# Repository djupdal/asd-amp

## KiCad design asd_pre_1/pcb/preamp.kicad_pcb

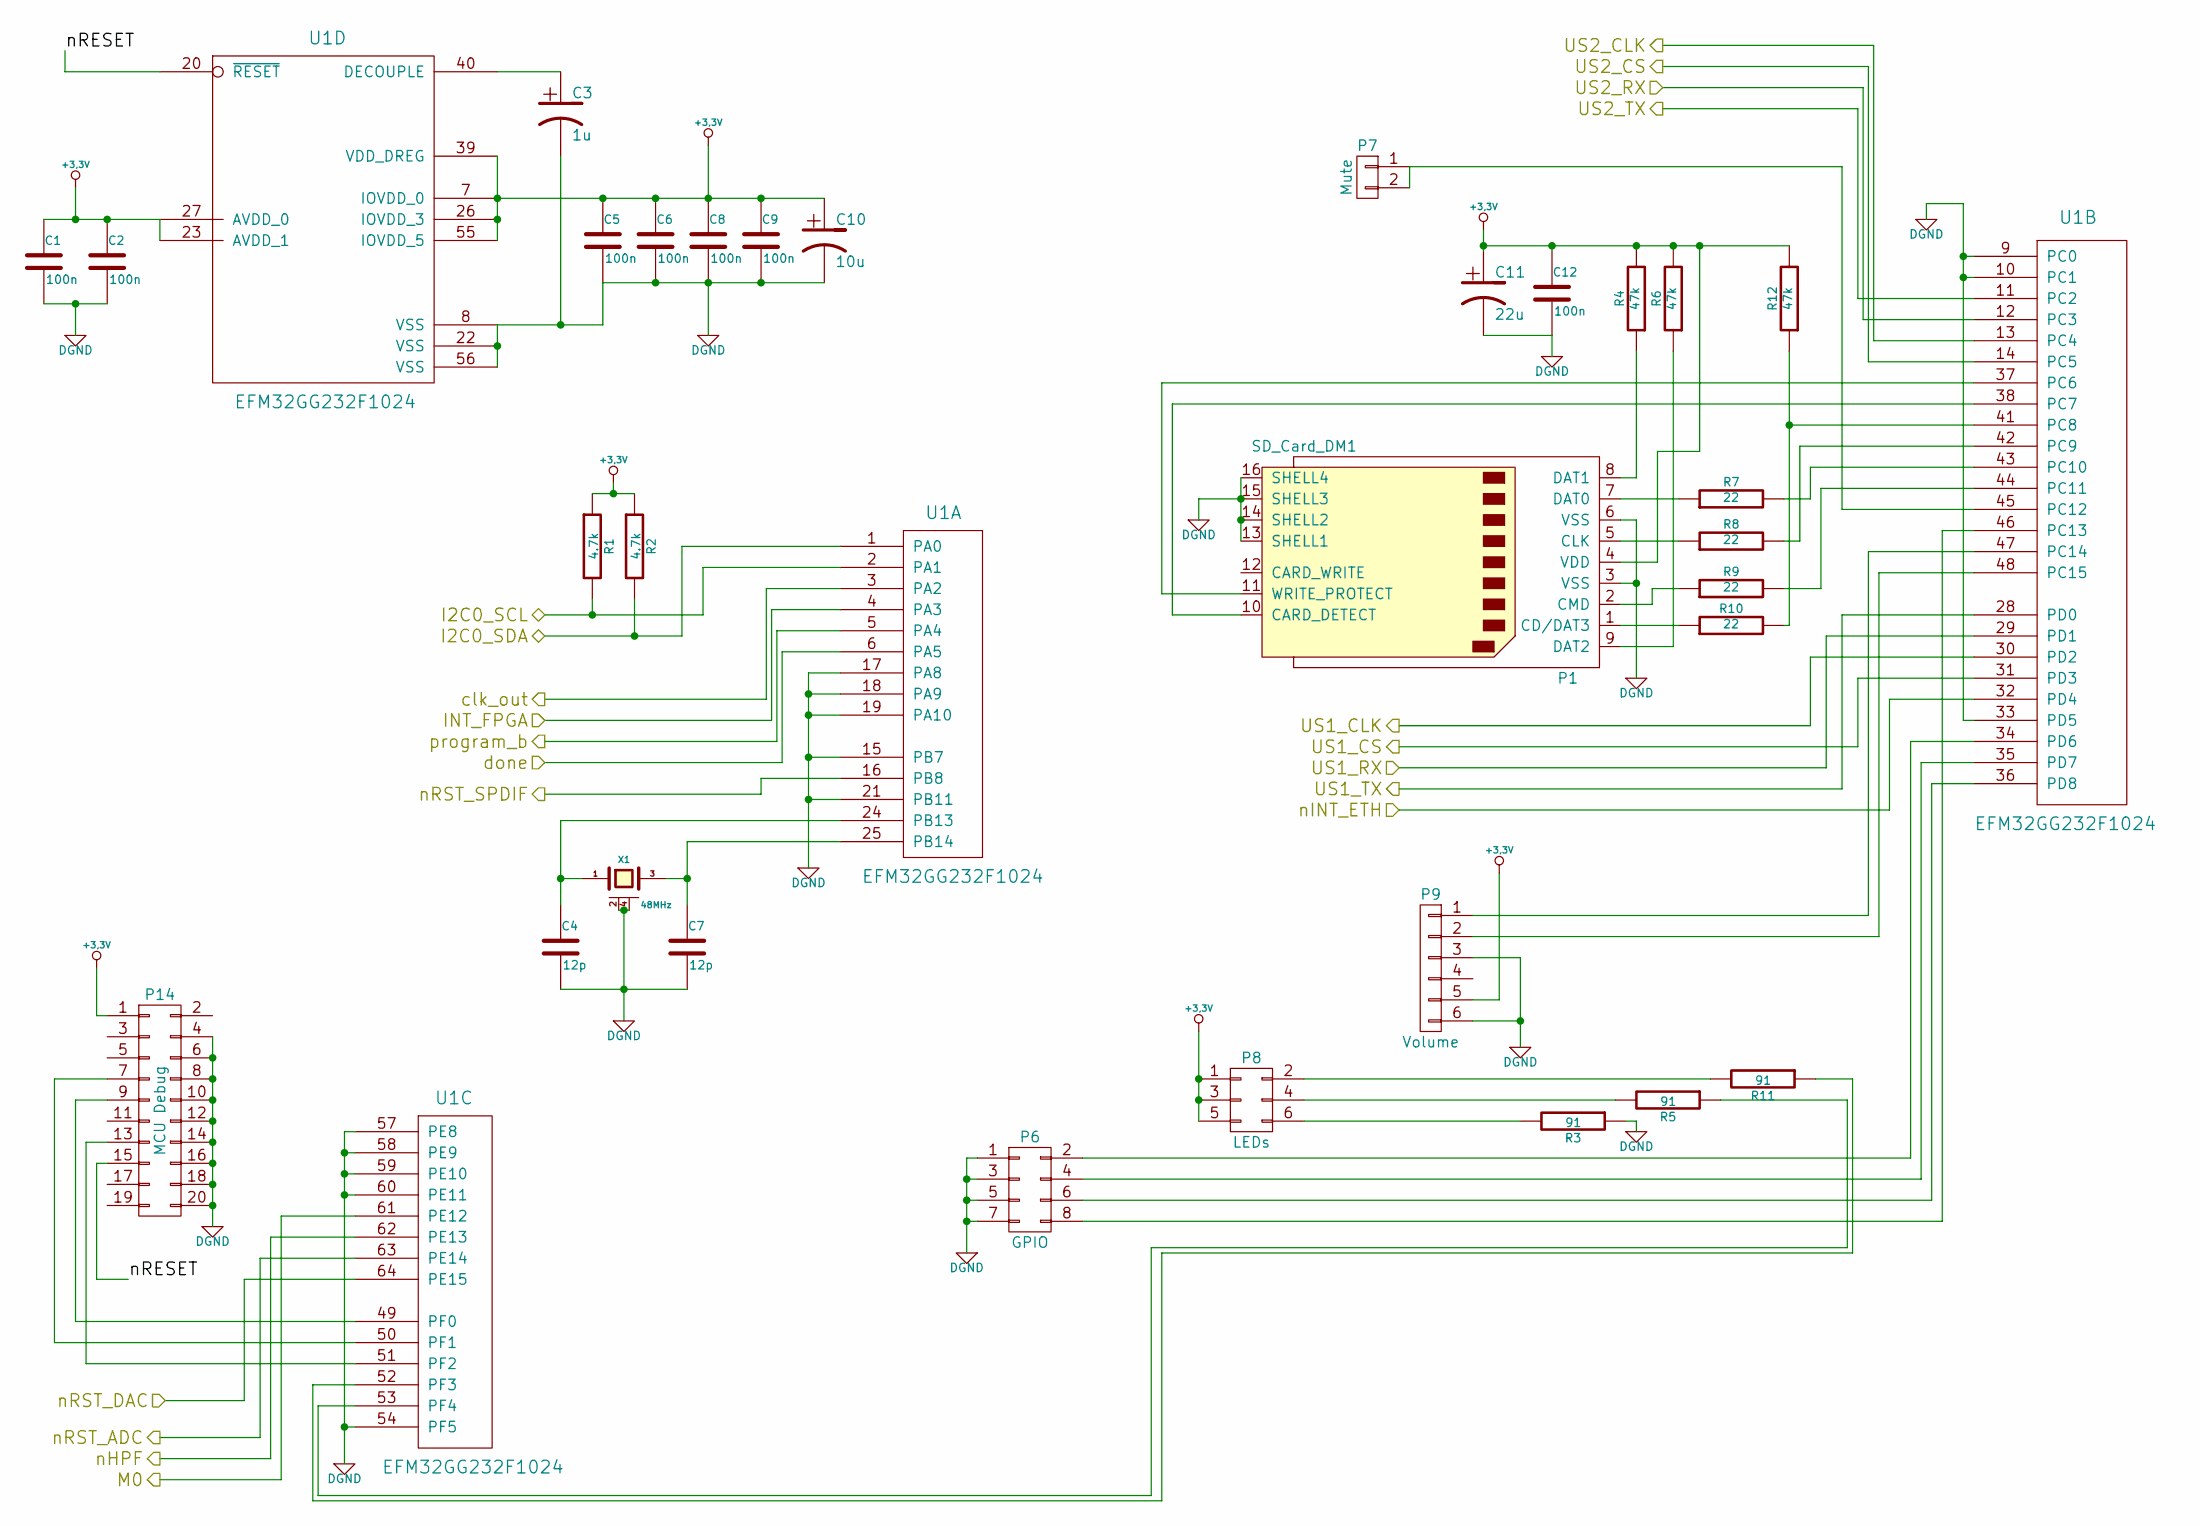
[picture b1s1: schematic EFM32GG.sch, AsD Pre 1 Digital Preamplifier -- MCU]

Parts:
C1, C2, C5, C6, C8, C9, C12: 100n; C_0603_HandSoldering
C3: 1u; C_0805_HandSoldering
C4, C7: 12p; C_0603_HandSoldering
C10: 10u; C_0805_HandSoldering
C11: 22u; C_0805_HandSoldering
P1: SD_Card_DM1; DM1AA-SF-PEJ
P6: GPIO; Pin_Header_Straight_2x04
P7: Mute; Pin_Header_Straight_1x02
P8: LEDs; Pin_Header_Straight_2x03
P9: Volume; Pin_Header_Straight_2x03
P14: MCU Debug; Pin_Header_Straight_2x10
R1, R2: 4.7k; R_0805_HandSoldering
R3, R5, R11: 91; R_0805_HandSoldering
R4, R6, R12: 47k; R_0805_HandSoldering
R7, R8, R9, R10: 22; R_0805_HandSoldering
U1: EFM32GG232F1024; QFP64
X1: 48MHz; XTAL_SMD

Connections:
+3.3V: C1.1, C2.1, C5.1, C6.1, C8.1, C9.1, C10.1, C11.1, C12.1, P1.4 (VDD), P8.1, P8.3, P8.5, P9.5, P14.1, R1.1, R2.1, R4.2, R6.2, R12.2, U1.7 (IOVDD_0), U1.23 (AVDD_1), U1.26 (IOVDD_3), U1.27 (AVDD_0), U1.39 (VDD_DREG), U1.55 (IOVDD_5); also elsewhere on the board
/ADC/M0: U1.61 (PE12); also elsewhere on the board
/ADC/nHPF: U1.62 (PE13); also elsewhere on the board
/ADC/nRST: U1.63 (PE14); also elsewhere on the board
/DAC/nRST: U1.64 (PE15); also elsewhere on the board
/EFM32GG/I2C0_SCL: R1.2, U1.2 (PA1); also elsewhere on the board
/EFM32GG/I2C0_SDA: R2.2, U1.1 (PA0); also elsewhere on the board
/EFM32GG/US1_CS: U1.31 (PD3); also elsewhere on the board
/EFM32GG/US2_CS: U1.14 (PC5); also elsewhere on the board
/EFM32GG/done: U1.6 (PA5); also elsewhere on the board
/EFM32GG/nRESET: P14.15, U1.20 (~RESET~)
/EFM32GG/program_b: U1.5 (PA4); also elsewhere on the board
/ETH/SCK: U1.30 (PD2); also elsewhere on the board
/ETH/SI: U1.28 (PD0); also elsewhere on the board
/ETH/SO: U1.29 (PD1); also elsewhere on the board
/ETH/nINT: U1.32 (PD4); also elsewhere on the board
/FPGA/INT: U1.4 (PA3); also elsewhere on the board
/FPGA/MISO: U1.12 (PC3); also elsewhere on the board
/FPGA/MOSI: U1.11 (PC2); also elsewhere on the board
/FPGA/SCLK: U1.13 (PC4); also elsewhere on the board
/FPGA/clk: U1.3 (PA2); also elsewhere on the board
/SPDIF/nRST: U1.16 (PB8); also elsewhere on the board
DGND: C1.2, C2.2, C3.2, C4.2, C5.2, C6.2, C7.2, C8.2, C9.2, C10.2, C11.2, C12.2, P1.3 (VSS), P1.6 (VSS), P1.13 (SHELL1), P1.14 (SHELL2), P1.15 (SHELL3), P1.16 (SHELL4), P6.1, P6.3, P6.5, P6.7, P9.3, P9.6, P14.4, P14.6, P14.8, P14.10, P14.12, P14.14, P14.16, P14.18, P14.20, R3.1, U1.8 (VSS), U1.9 (PC0), U1.10 (PC1), U1.15 (PB7), U1.17 (PA8), U1.18 (PA9), U1.19 (PA10), U1.21 (PB11), U1.22 (VSS), U1.33 (PD5), U1.54 (PF5), U1.56 (VSS), U1.57 (PE8), U1.58 (PE9), U1.59 (PE10), U1.60 (PE11), X1.2 (GND), X1.4 (GND); also elsewhere on the board
unnamed: C3.1, U1.40 (DECOUPLE)
unnamed: C4.1, U1.24 (PB13), X1.1
unnamed: C7.1, U1.25 (PB14), X1.3
unnamed: P1.1 (CD/DAT3), R10.1
unnamed: P1.2 (CMD), R9.1
unnamed: P1.5 (CLK), R8.1
unnamed: P1.7 (DAT0), R7.1
unnamed: P1.8 (DAT1), R4.1
unnamed: P1.9 (DAT2), R6.1
unnamed: P1.10 (CARD_DETECT), U1.38 (PC7)
unnamed: P1.11 (WRITE_PROTECT), U1.37 (PC6)
unnamed: P6.2, U1.34 (PD6)
unnamed: P6.4, U1.35 (PD7)
unnamed: P6.6, U1.36 (PD8)
unnamed: P6.8, U1.46 (PC13)
unnamed: P7.1, P7.2, U1.45 (PC12)
unnamed: P8.2, R11.2
unnamed: P8.4, R5.2
unnamed: P8.6, R3.2
unnamed: P9.1, U1.47 (PC14)
unnamed: P9.2, U1.48 (PC15)
unnamed: P14.7, U1.50 (PF1)
unnamed: P14.9, U1.49 (PF0)
unnamed: P14.13, U1.51 (PF2)
unnamed: R5.1, U1.53 (PF4)
unnamed: R7.2, U1.43 (PC10)
unnamed: R8.2, U1.42 (PC9)
unnamed: R9.2, U1.44 (PC11)
unnamed: R10.2, R12.1, U1.41 (PC8)
unnamed: R11.1, U1.52 (PF3)

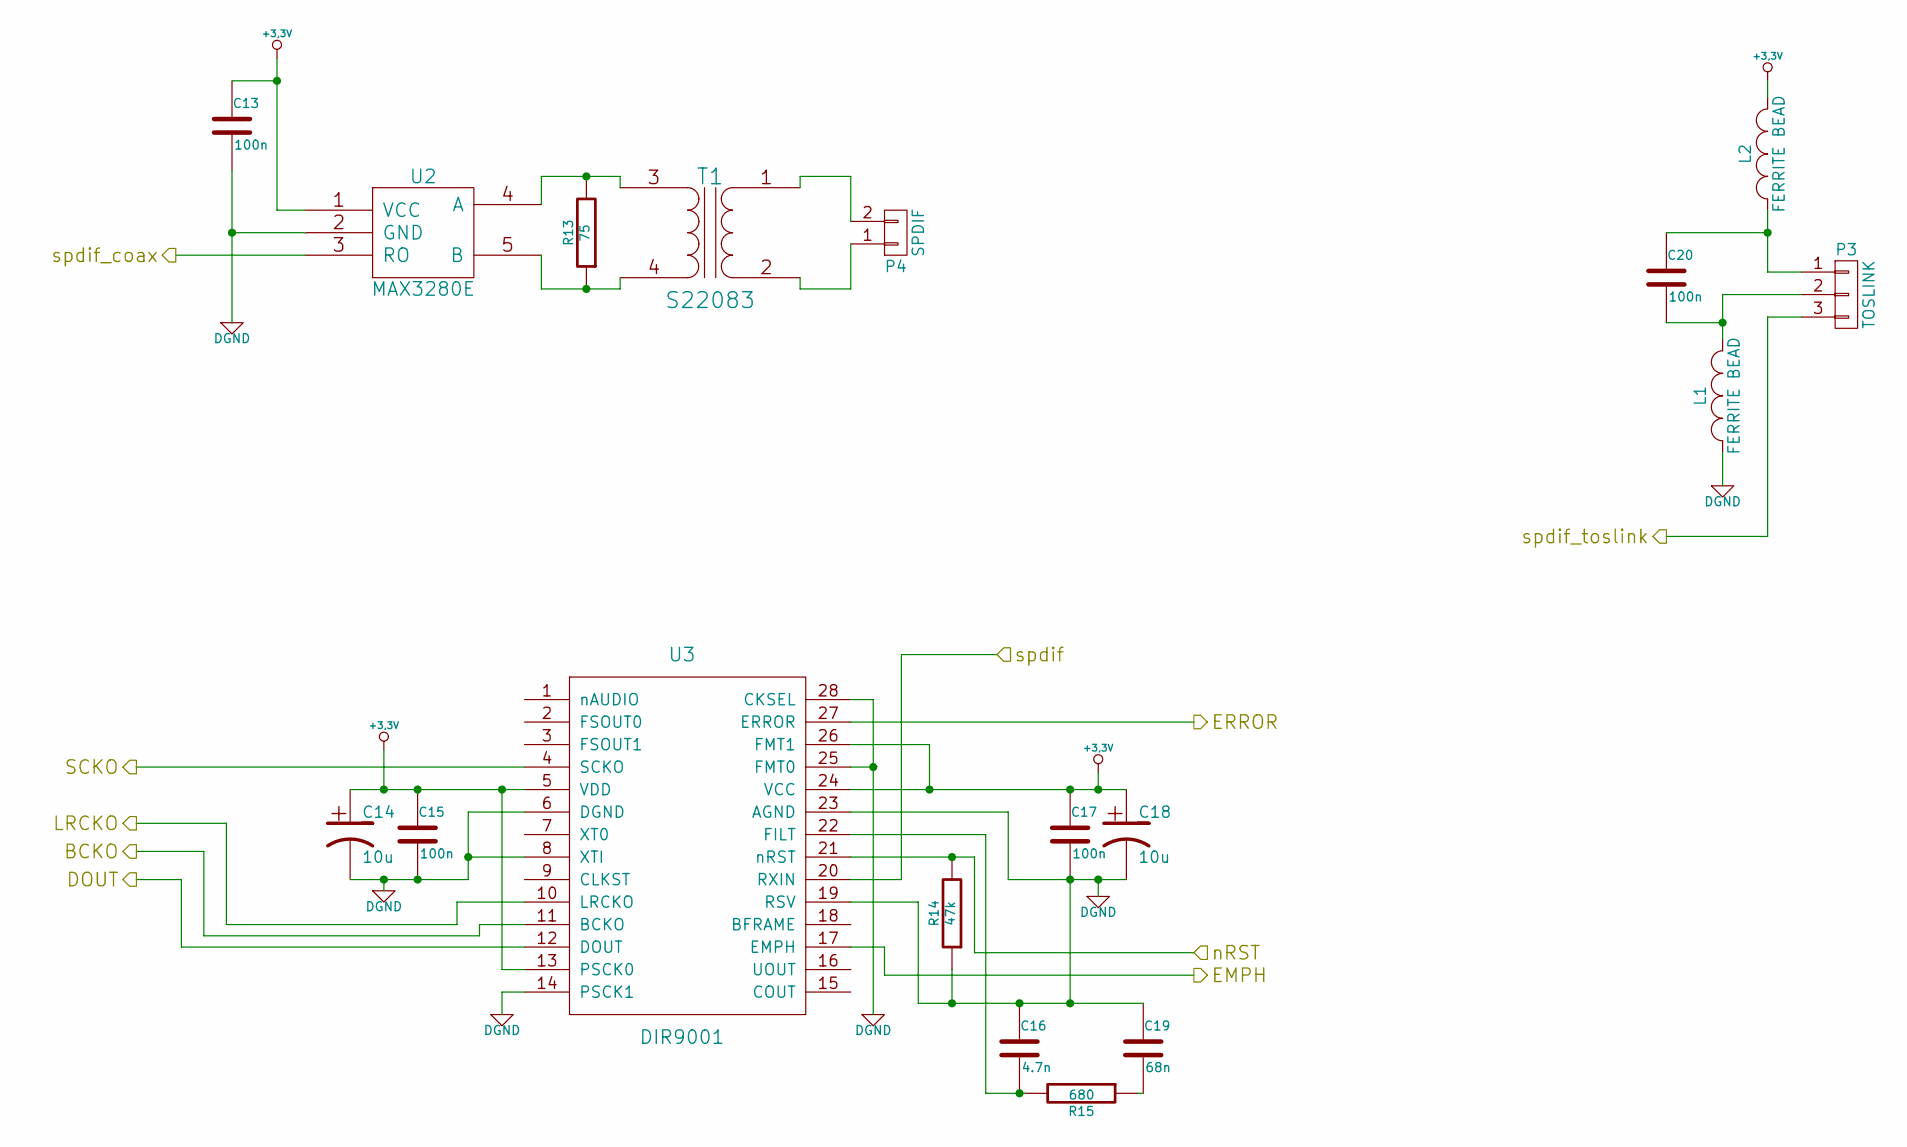
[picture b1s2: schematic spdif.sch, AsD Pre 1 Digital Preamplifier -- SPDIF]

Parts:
C13, C15, C17, C20: 100n; C_0603_HandSoldering
C14, C18: 10u; C_0805_HandSoldering
C16: 4.7n; C_0603_HandSoldering
C19: 68n; C_0603_HandSoldering
L1, L2: FERRITE BEAD; R_0805_HandSoldering
P3: TOSLINK; PLR135T
P4: SPDIF; RCA
R13: 75; R_0805_HandSoldering
R14: 47k; R_0805_HandSoldering
R15: 680; R_0805_HandSoldering
T1: S22083
U2: MAX3280E; SOT-23-5
U3: DIR9001; TSSOP-28_4.4x9.7mm_Pitch0.65mm

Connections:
+3.3V: C13.1, C14.1, C15.1, C17.1, C18.1, L2.2, U2.1 (VCC), U3.5 (VDD), U3.13 (PSCK0), U3.24 (VCC), U3.26 (FMT1); also elsewhere on the board
/FPGA/BCKI1: U3.11 (BCKO); also elsewhere on the board
/FPGA/DIN1: U3.12 (DOUT); also elsewhere on the board
/FPGA/EMPH: U3.17 (EMPH); also elsewhere on the board
/FPGA/ERROR: U3.27 (ERROR); also elsewhere on the board
/FPGA/LRCKI1: U3.10 (LRCKO); also elsewhere on the board
/FPGA/SCKI1: U3.4 (SCKO); also elsewhere on the board
/FPGA/spdif: U3.20 (RXIN); also elsewhere on the board
/FPGA/spdif_coax: U2.3 (RO); also elsewhere on the board
/FPGA/spdif_toslink: P3.3; also elsewhere on the board
/SPDIF/nRST: R14.2, U3.21 (nRST); also elsewhere on the board
DGND: C13.2, C14.2, C15.2, C16.1, C17.2, C18.2, C19.1, L1.1, R14.1, U2.2 (GND), U3.6 (DGND), U3.8 (XTI), U3.14 (PSCK1), U3.19 (RSV), U3.23 (AGND), U3.25 (FMT0), U3.28 (CKSEL); also elsewhere on the board
unnamed: C16.2, R15.2, U3.22 (FILT)
unnamed: C19.2, R15.1
unnamed: C20.1, L2.1, P3.1
unnamed: C20.2, L1.2, P3.2
unnamed: P4.1, T1.2 (AB)
unnamed: P4.2, T1.1 (AA)
unnamed: R13.1, T1.4 (SA), U2.5 (B)
unnamed: R13.2, T1.3 (SB), U2.4 (A)

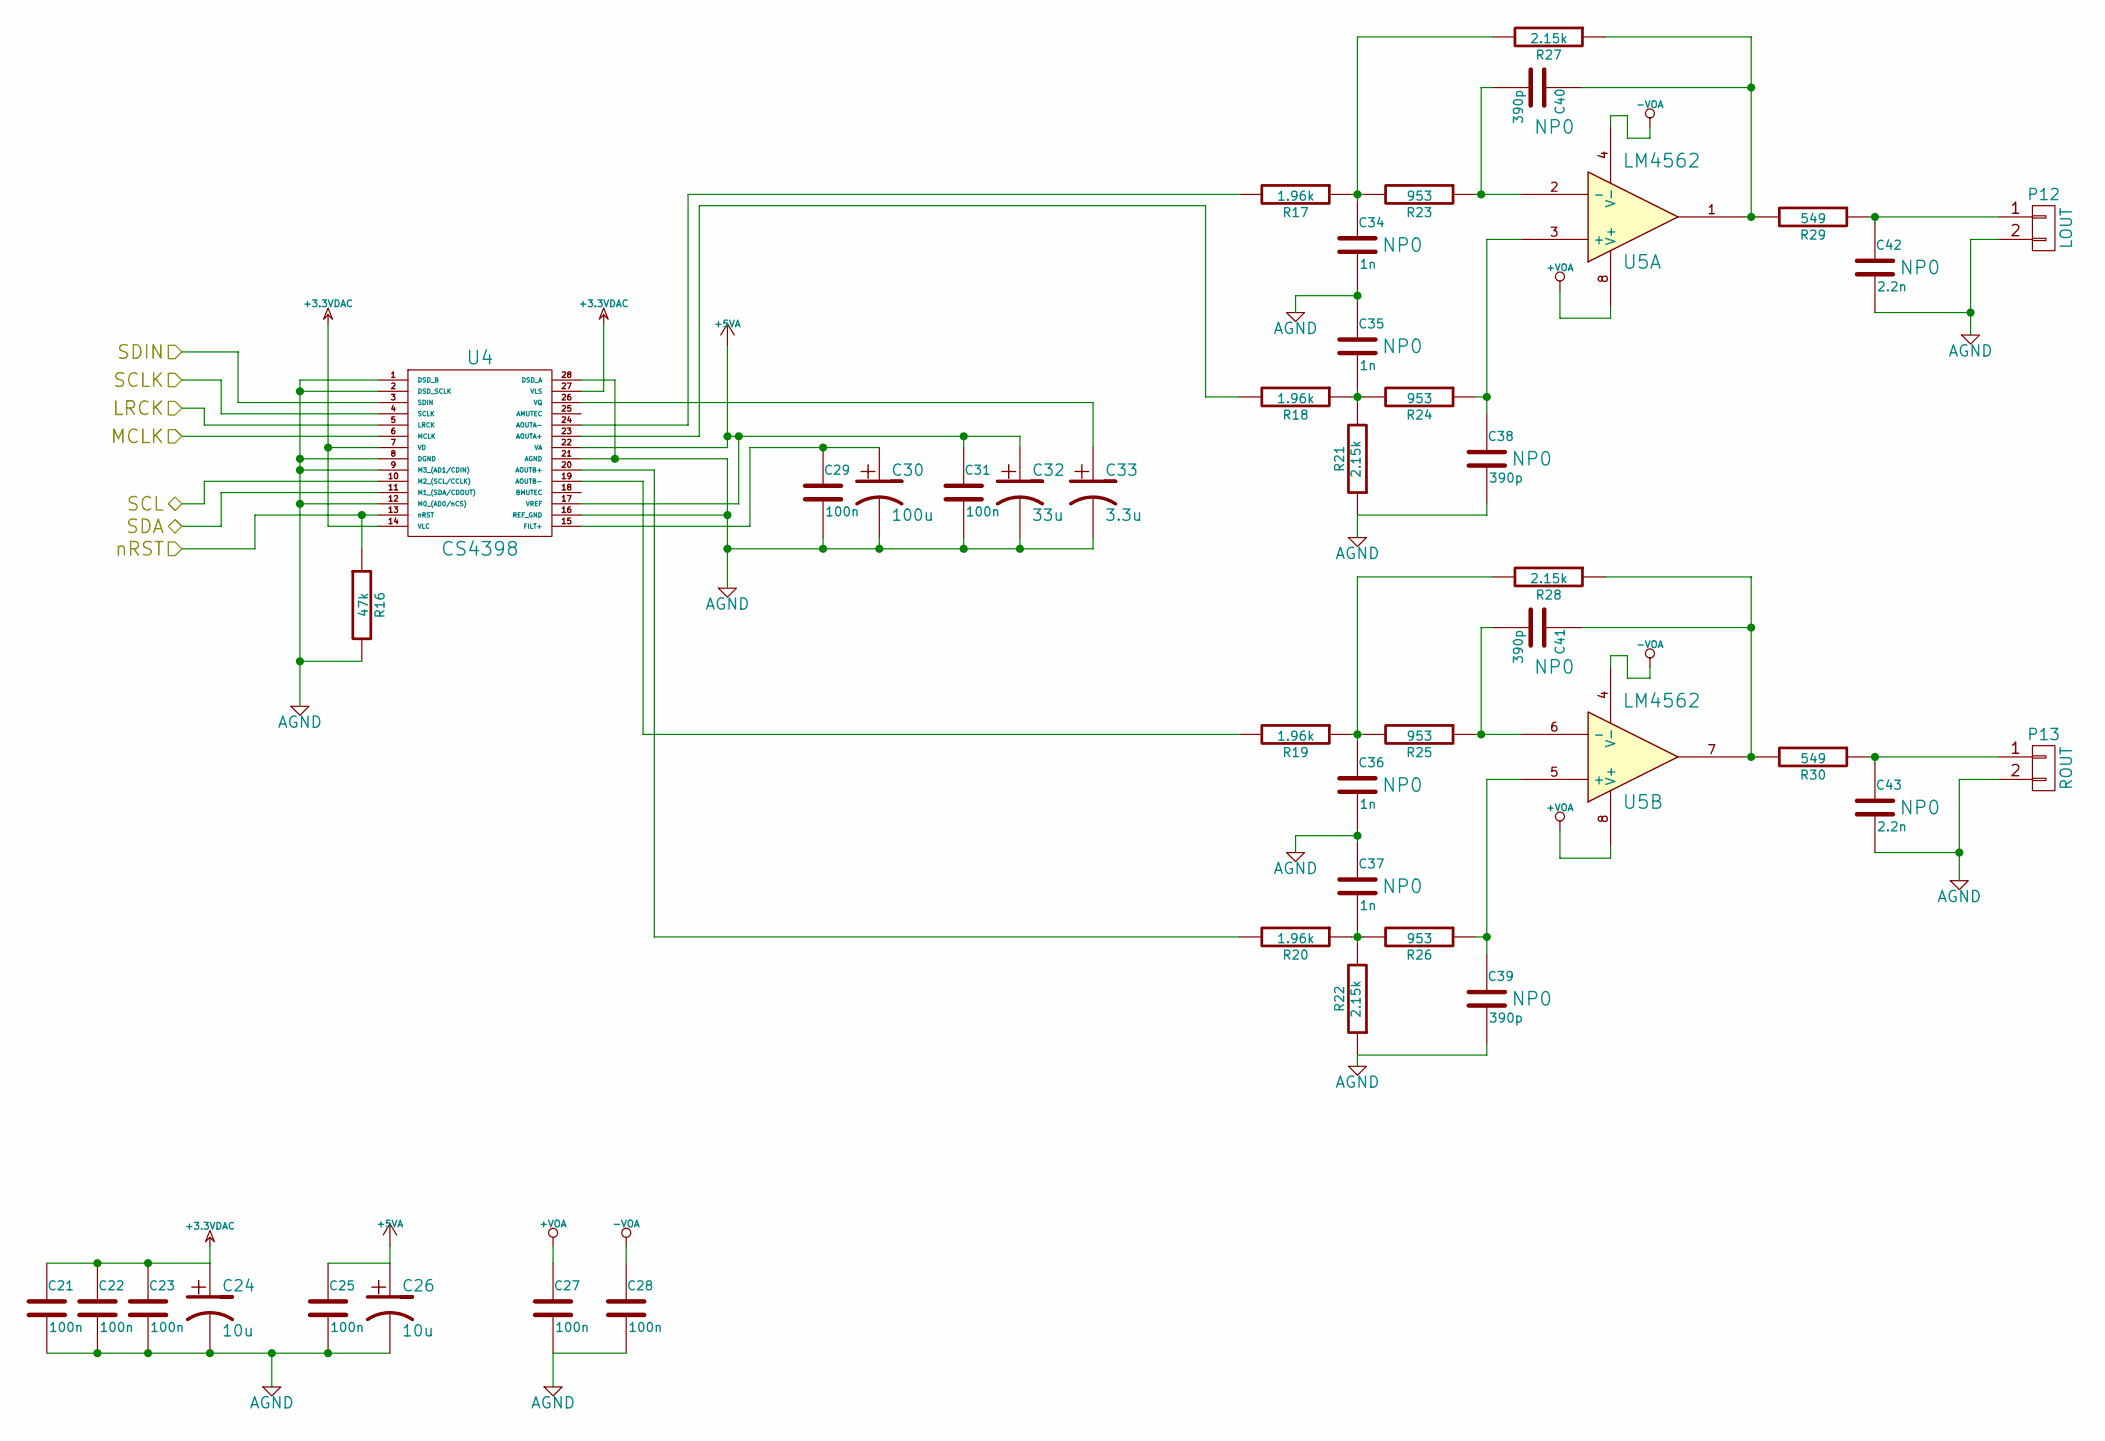
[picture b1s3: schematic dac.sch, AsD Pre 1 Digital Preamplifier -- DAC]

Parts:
C21, C22, C23, C25, C27, C28, C29, C31: 100n; C_0603_HandSoldering
C24, C26: 10u; C_0805_HandSoldering
C30: 100u; TantalC_SizeB_EIA-3528_HandSoldering
C32: 33u; C_1210_HandSoldering
C33: 3.3u; C_0805_HandSoldering
C34, C35, C36, C37: 1n; C_0603_HandSoldering
C38, C39, C40, C41: 390p; C_0603_HandSoldering
C42, C43: 2.2n; C_0603_HandSoldering
P12: LOUT; Terminal_Block_2_2.5mm
P13: ROUT; Terminal_Block_2_2.5mm
R16: 47k; R_0805_HandSoldering
R17, R18, R19, R20: 1.96k; R_0805_HandSoldering
R21, R22, R27, R28: 2.15k; R_0805_HandSoldering
R23, R24, R25, R26: 953; R_0805_HandSoldering
R29, R30: 549; R_0805_HandSoldering
U4: CS4398; TSSOP-28_4.4x9.7mm_Pitch0.65mm
U5: LM4562; SOIC-8-W

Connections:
+3.3V: C21.1, C22.1, C23.1, C24.1, U4.7 (VD), U4.14 (VLC), U4.27 (VLS); also elsewhere on the board
+5VA: C25.1, C26.1, C31.1, C32.1, U4.17 (VREF), U4.22 (VA); also elsewhere on the board
+VOA: C27.1, U5.8 (V+); also elsewhere on the board
-VOA: C28.1, U5.4 (V-); also elsewhere on the board
/DAC/LRCK: U4.5 (LRCK); also elsewhere on the board
/DAC/MCLK: U4.6 (MCLK); also elsewhere on the board
/DAC/nRST: R16.1, U4.13 (nRST); also elsewhere on the board
/EFM32GG/I2C0_SCL: U4.10 (M2_(SCL/CCLK)); also elsewhere on the board
/EFM32GG/I2C0_SDA: U4.11 (M1_(SDA/CDOUT)); also elsewhere on the board
/FPGA/BCKO: U4.4 (SCLK); also elsewhere on the board
/FPGA/DOUT: U4.3 (SDIN); also elsewhere on the board
DGND: C21.2, C22.2, C23.2, C24.2, C25.2, C26.2, C27.2, C28.2, C29.2, C30.2, C31.2, C32.2, C33.2, C34.2, C35.1, C36.2, C37.1, C38.2, C39.2, C42.2, C43.2, P12.2, P13.2, R16.2, R21.1, R22.1, U4.1 (DSD_B), U4.2 (DSD_SCLK), U4.8 (DGND), U4.9 (M3_(AD1/CDIN)), U4.12 (M0_(AD0/nCS)), U4.16 (REF_GND), U4.21 (AGND), U4.28 (DSD_A); also elsewhere on the board
unnamed: C29.1, C30.1, U4.15 (FILT+)
unnamed: C33.1, U4.26 (VQ)
unnamed: C34.1, R17.1, R23.2, R27.2
unnamed: C35.2, R18.1, R21.2, R24.2
unnamed: C36.1, R19.1, R25.2, R28.2
unnamed: C37.2, R20.1, R22.2, R26.2
unnamed: C38.1, R24.1, U5.3 (+)
unnamed: C39.1, R26.1, U5.5 (+)
unnamed: C40.1, R27.1, R29.2, U5.1
unnamed: C40.2, R23.1, U5.2 (-)
unnamed: C41.1, R28.1, R30.2, U5.7
unnamed: C41.2, R25.1, U5.6 (-)
unnamed: C42.1, P12.1, R29.1
unnamed: C43.1, P13.1, R30.1
unnamed: R17.2, U4.24 (AOUTA-)
unnamed: R18.2, U4.23 (AOUTA+)
unnamed: R19.2, U4.19 (AOUTB-)
unnamed: R20.2, U4.20 (AOUTB+)

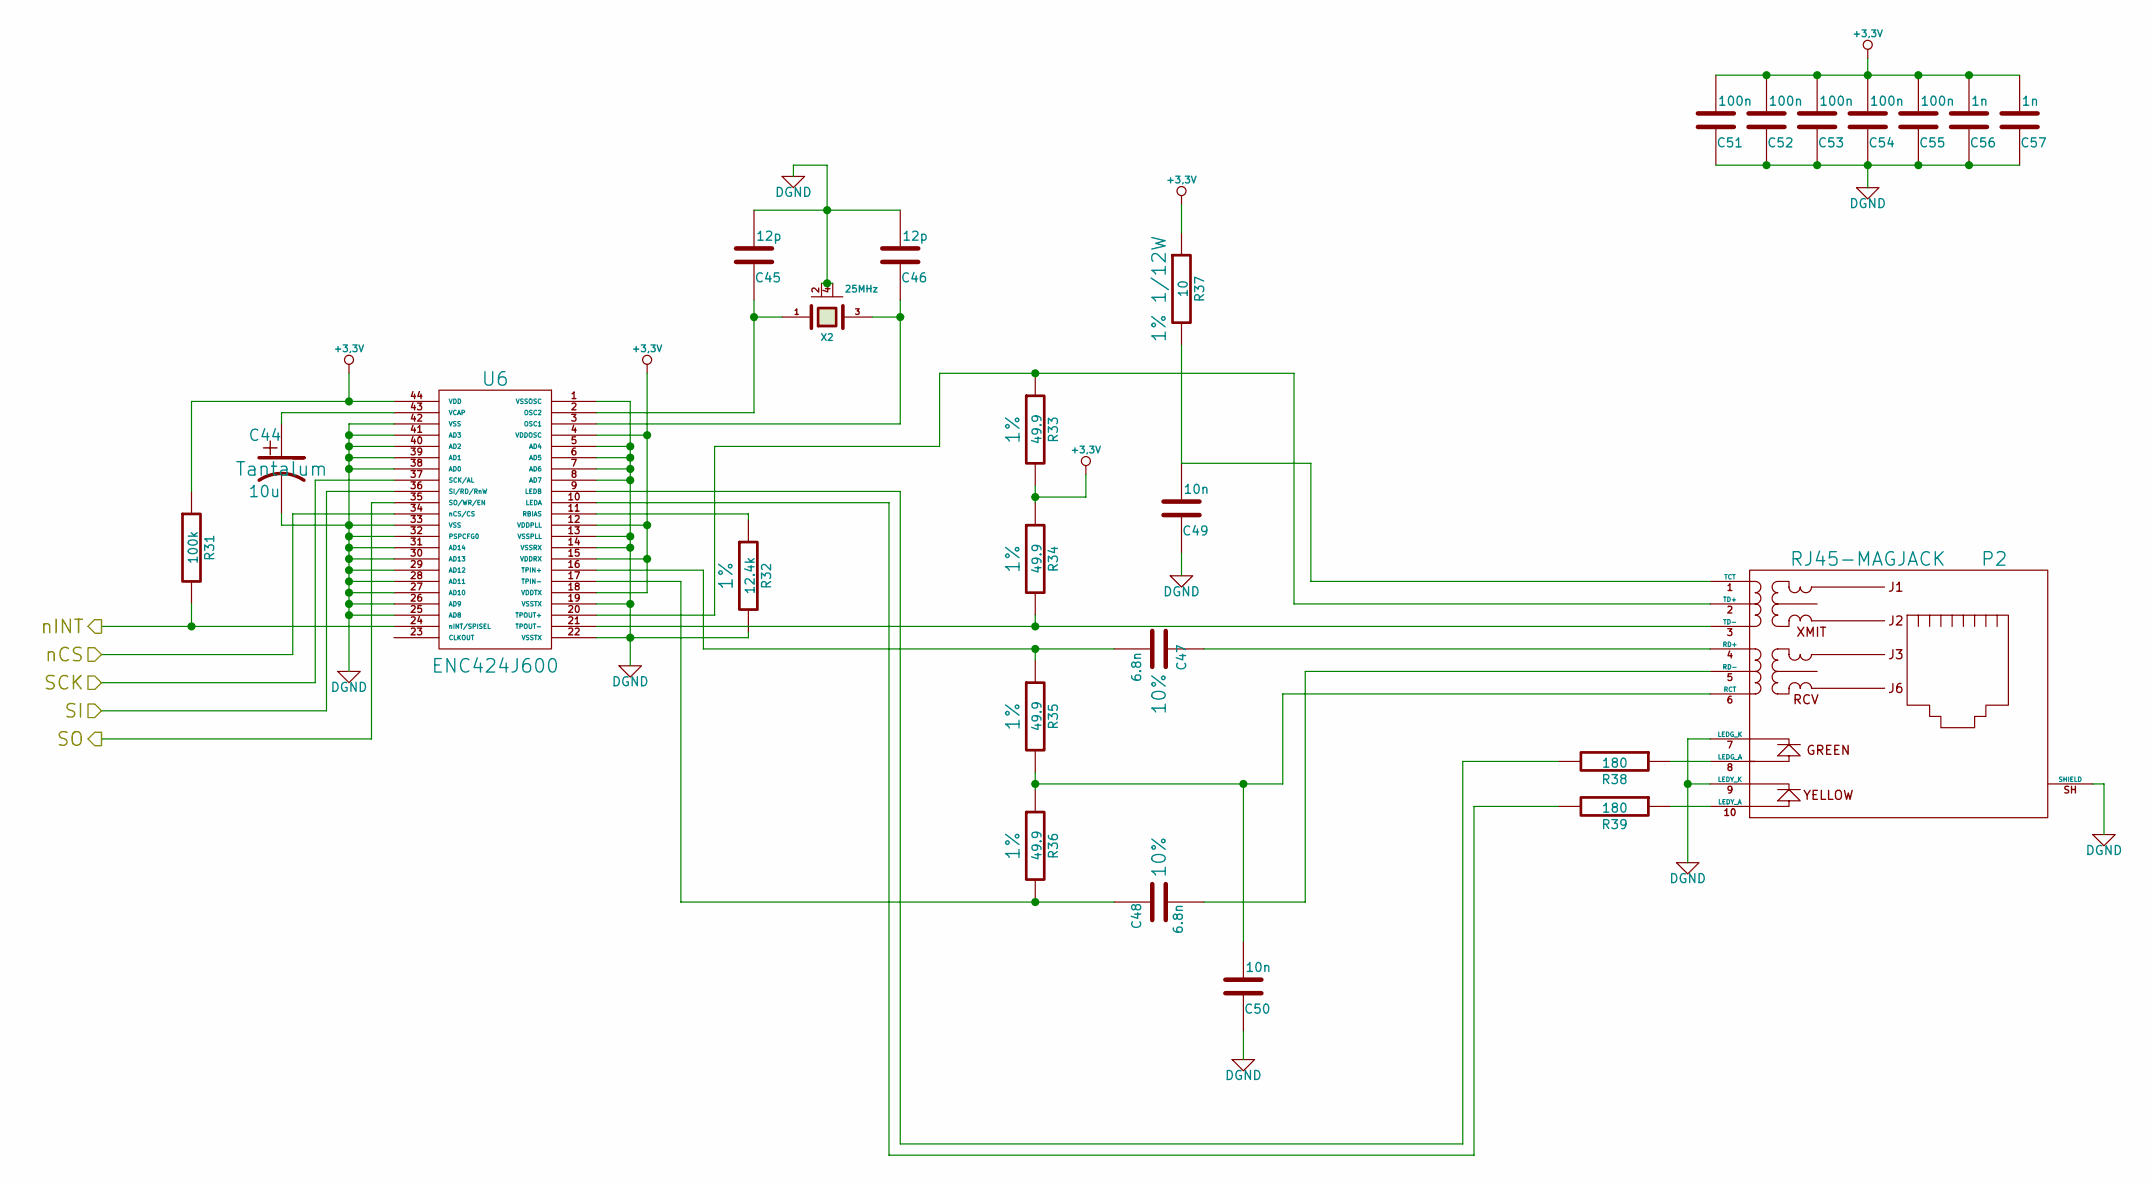
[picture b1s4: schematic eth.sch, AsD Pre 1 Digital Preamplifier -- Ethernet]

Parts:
C44: 10u; C_0805_HandSoldering
C45, C46: 12p; C_0603_HandSoldering
C47, C48: 6.8n; C_0603_HandSoldering
C49, C50: 10n; C_0603_HandSoldering
C51, C52, C53, C54, C55: 100n; C_0603_HandSoldering
C56, C57: 1n; C_0603_HandSoldering
P2: RJ45-MAGJACK; 08B0-1D1T-06-F
R31: 100k; R_0805_HandSoldering
R32: 12.4k; R_0805_HandSoldering
R33, R34, R35, R36: 49.9; R_0805_HandSoldering
R37: 10; R_0805_HandSoldering
R38, R39: 180; R_0805_HandSoldering
U6: ENC424J600; TQFP-44_10x10mm_Pitch0.8mm
X2: 25MHz; XTAL_SMD

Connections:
+3.3V: C51.2, C52.2, C53.2, C54.2, C55.2, C56.2, C57.2, R31.1, R33.2, R34.1, R37.1, U6.4 (VDDOSC), U6.12 (VDDPLL), U6.15 (VDDRX), U6.18 (VDDTX), U6.44 (VDD); also elsewhere on the board
/EFM32GG/US1_CS: U6.34 (nCS/CS); also elsewhere on the board
/ETH/SCK: U6.37 (SCK/AL); also elsewhere on the board
/ETH/SI: U6.36 (SI/RD/RnW); also elsewhere on the board
/ETH/SO: U6.35 (SO/WR/EN); also elsewhere on the board
/ETH/nINT: R31.2, U6.24 (nINT/SPISEL); also elsewhere on the board
DGND: C44.2, C45.2, C46.2, C49.1, C50.1, C51.1, C52.1, C53.1, C54.1, C55.1, C56.1, C57.1, P2.7 (LEDG_K), P2.9 (LEDY_K), P2.SH (SHIELD), R32.2, U6.1 (VSSOSC), U6.5 (AD4), U6.6 (AD5), U6.7 (AD6), U6.8 (AD7), U6.13 (VSSPLL), U6.14 (VSSRX), U6.19 (VSSTX), U6.22 (VSSTX), U6.25 (AD8), U6.26 (AD9), U6.27 (AD10), U6.28 (AD11), U6.29 (AD12), U6.30 (AD13), U6.31 (AD14), U6.32 (PSPCFG0), U6.33 (VSS), U6.38 (AD0), U6.39 (AD1), U6.40 (AD2), U6.41 (AD3), U6.42 (VSS), X2.2 (GND), X2.4 (GND); also elsewhere on the board
unnamed: C44.1, U6.43 (VCAP)
unnamed: C45.1, U6.2 (OSC2), X2.1
unnamed: C46.1, U6.3 (OSC1), X2.3
unnamed: C47.1, P2.4 (RD+)
unnamed: C47.2, R35.1, U6.16 (TPIN+)
unnamed: C48.1, R36.2, U6.17 (TPIN-)
unnamed: C48.2, P2.5 (RD-)
unnamed: C49.2, P2.1 (TCT), R37.2
unnamed: C50.2, P2.6 (RCT), R35.2, R36.1
unnamed: P2.2 (TD+), R33.1, U6.20 (TPOUT+)
unnamed: P2.3 (TD-), R34.2, U6.21 (TPOUT-)
unnamed: P2.8 (LEDG_A), R38.1
unnamed: P2.10 (LEDY_A), R39.1
unnamed: R32.1, U6.11 (RBIAS)
unnamed: R38.2, U6.9 (LEDB)
unnamed: R39.2, U6.10 (LEDA)

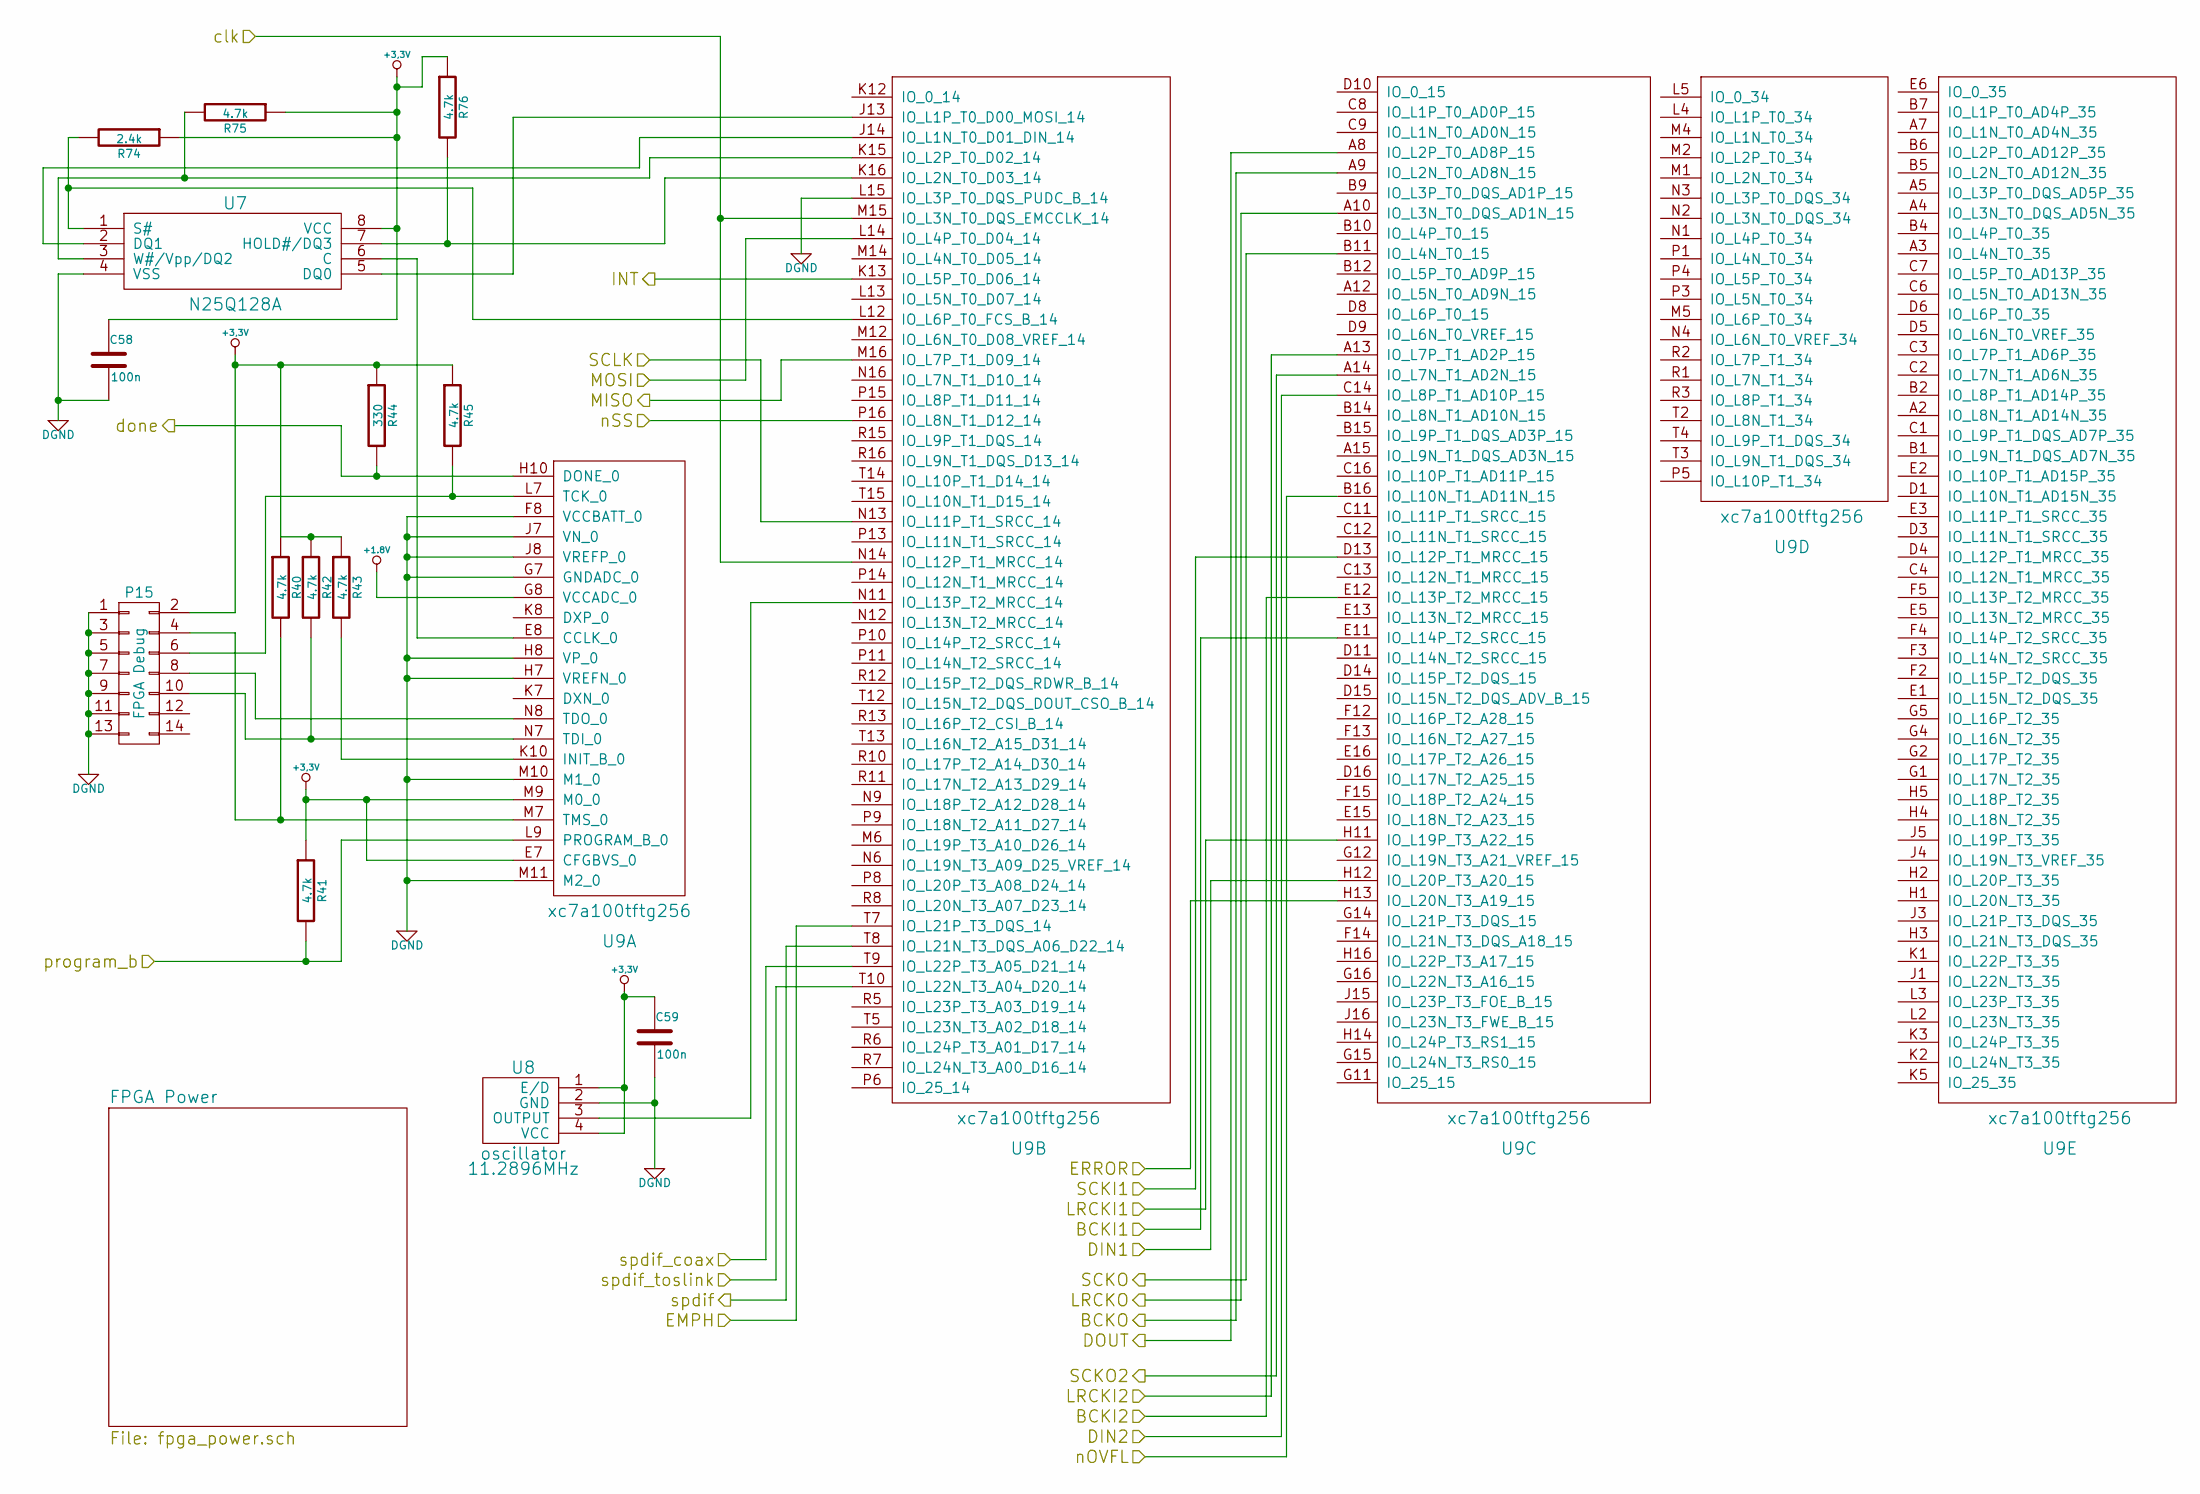
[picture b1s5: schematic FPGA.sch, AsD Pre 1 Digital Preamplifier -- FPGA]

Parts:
C58, C59: 100n; C_0603_HandSoldering
P15: FPGA Debug; FPGA_debug
R40, R41, R42, R43, R45, R75, R76: 4.7k; R_0805_HandSoldering
R44: 330; R_0805_HandSoldering
R74: 2.4k; R_0805_HandSoldering
U7: N25Q128A; SOIJ-8_5.3x5.3mm_Pitch1.27mm
U8: oscillator; OSC_SMD
U9: xc7a100tftg256; FTG256

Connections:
+1.8V: U9.G8 (VCCADC_0); also elsewhere on the board
+3.3V: C58.1, C59.1, P15.2, R40.1, R41.1, R42.1, R43.1, R44.1, R45.1, R74.1, R75.1, R76.1, U7.8 (VCC), U8.1 (E/D), U8.4 (VCC), U9.E7 (CFGBVS_0), U9.M9 (M0_0); also elsewhere on the board
/ADC/LRCK: U9.A13 (IO_L7P_T1_AD2P_15); also elsewhere on the board
/ADC/MCLK: U9.A14 (IO_L7N_T1_AD2N_15); also elsewhere on the board
/ADC/nOVFL: U9.B16 (IO_L10N_T1_AD11N_15); also elsewhere on the board
/DAC/LRCK: U9.A10 (IO_L3N_T0_DQS_AD1N_15); also elsewhere on the board
/DAC/MCLK: U9.B11 (IO_L4N_T0_15); also elsewhere on the board
/EFM32GG/US2_CS: U9.P16 (IO_L8N_T1_D12_14); also elsewhere on the board
/EFM32GG/done: R44.2, U9.H10 (DONE_0); also elsewhere on the board
/EFM32GG/program_b: R41.2, U9.L9 (PROGRAM_B_0); also elsewhere on the board
/FPGA/BCKI1: U9.E11 (IO_L14P_T2_SRCC_15); also elsewhere on the board
/FPGA/BCKI2: U9.E12 (IO_L13P_T2_MRCC_15); also elsewhere on the board
/FPGA/BCKO: U9.A9 (IO_L2N_T0_AD8N_15); also elsewhere on the board
/FPGA/DIN1: U9.H12 (IO_L20P_T3_A20_15); also elsewhere on the board
/FPGA/DIN2: U9.C14 (IO_L8P_T1_AD10P_15); also elsewhere on the board
/FPGA/DOUT: U9.A8 (IO_L2P_T0_AD8P_15); also elsewhere on the board
/FPGA/EMPH: U9.T7 (IO_L21P_T3_DQS_14); also elsewhere on the board
/FPGA/ERROR: U9.H13 (IO_L20N_T3_A19_15); also elsewhere on the board
/FPGA/INT: U9.K13 (IO_L5P_T0_D06_14); also elsewhere on the board
/FPGA/LRCKI1: U9.H11 (IO_L19P_T3_A22_15); also elsewhere on the board
/FPGA/MISO: U9.M16 (IO_L7P_T1_D09_14); also elsewhere on the board
/FPGA/MOSI: U9.L14 (IO_L4P_T0_D04_14); also elsewhere on the board
/FPGA/SCKI1: U9.D13 (IO_L12P_T1_MRCC_15); also elsewhere on the board
/FPGA/SCLK: U9.N13 (IO_L11P_T1_SRCC_14); also elsewhere on the board
/FPGA/clk: U9.M15 (IO_L3N_T0_DQS_EMCCLK_14), U9.N14 (IO_L12P_T1_MRCC_14); also elsewhere on the board
/FPGA/spdif: U9.T8 (IO_L21N_T3_DQS_A06_D22_14); also elsewhere on the board
/FPGA/spdif_coax: U9.T9 (IO_L22P_T3_A05_D21_14); also elsewhere on the board
/FPGA/spdif_toslink: U9.T10 (IO_L22N_T3_A04_D20_14); also elsewhere on the board
DGND: C58.2, C59.2, P15.1, P15.3, P15.5, P15.7, P15.9, P15.11, P15.13, U7.4 (VSS), U8.2 (GND), U9.F8 (VCCBATT_0), U9.G7 (GNDADC_0), U9.H7 (VREFN_0), U9.H8 (VP_0), U9.J7 (VN_0), U9.J8 (VREFP_0), U9.L15 (IO_L3P_T0_DQS_PUDC_B_14), U9.M10 (M1_0), U9.M11 (M2_0); also elsewhere on the board
unnamed: P15.4, R40.2, U9.M7 (TMS_0)
unnamed: P15.6, R45.2, U9.L7 (TCK_0)
unnamed: P15.8, U9.N8 (TDO_0)
unnamed: P15.10, R42.2, U9.N7 (TDI_0)
unnamed: R43.2, U9.K10 (INIT_B_0)
unnamed: R74.2, U7.1 (S#), U9.L12 (IO_L6P_T0_FCS_B_14)
unnamed: R75.2, U7.3 (W#/Vpp/DQ2), U9.K15 (IO_L2P_T0_D02_14)
unnamed: R76.2, U7.7 (HOLD#/DQ3), U9.K16 (IO_L2N_T0_D03_14)
unnamed: U7.2 (DQ1), U9.J14 (IO_L1N_T0_D01_DIN_14)
unnamed: U7.5 (DQ0), U9.J13 (IO_L1P_T0_D00_MOSI_14)
unnamed: U7.6 (C), U9.E8 (CCLK_0)
unnamed: U8.3 (OUTPUT), U9.N11 (IO_L13P_T2_MRCC_14)
